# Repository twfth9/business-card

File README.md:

# business-card
Business Card Designs

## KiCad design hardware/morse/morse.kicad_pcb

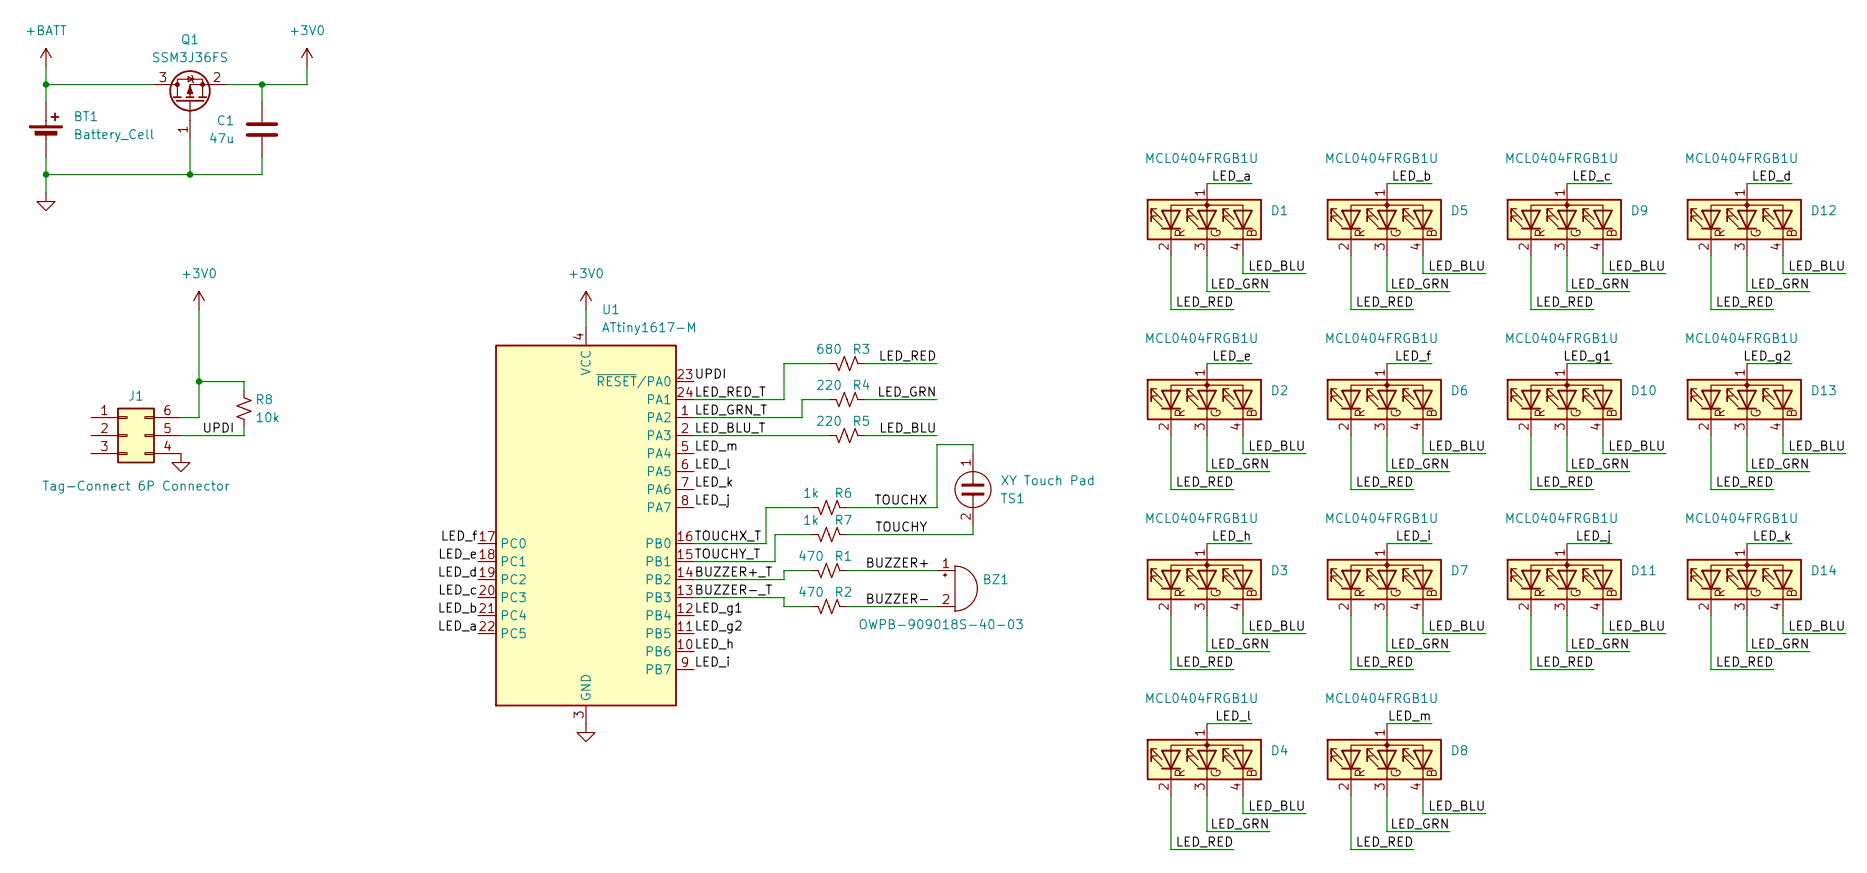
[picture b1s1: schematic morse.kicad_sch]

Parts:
BT1: Battery_Cell; CR2032_Holder
BZ1: OWPB-909018S-40-03; OWPB-909018S_recessed
C1: 47u; C_0805_2012Metric; Partnumber C16780; LCSC C16780
D1, D2, D3, D4, D5, D6, D7, D8, D9, D10, D11, D12, D13, D14: MCL0404FRGB1U; DigiKey 2679-MCL0404FRGB1U-CT-ND
J1: Tag-Connect 6P Connector; TC2030-IDC-NL_6P
Q1: SSM3J36FS; SOT-416; DigiKey SSM3J36FSLFCT-ND
R1, R2: 470; Worthington_R_0402
R3: 680; Worthington_R_0402
R4, R5: 220; Worthington_R_0402
R6, R7: 1k; Worthington_R_0402
R8: 10k
TS1: XY Touch Pad; TouchPad_12mm_XY
U1: ATtiny1617-M; QFN-24-1EP_4x4mm_P0.5mm_EP2.6x2.6mm

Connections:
+3V0: C1.1, J1.6, Q1.2 (S), R8.1, U1.4 (VCC)
+BATT: BT1.1 (+), Q1.3 (D)
/BUZZER+: BZ1.1 (+), R1.2
/BUZZER+_T: R1.1, U1.14 (PB2)
/BUZZER-: BZ1.2 (-), R2.2
/BUZZER-_T: R2.1, U1.13 (PB3)
/LED_BLU: D1.4 (BK), D2.4 (BK), D3.4 (BK), D4.4 (BK), D5.4 (BK), D6.4 (BK), D7.4 (BK), D8.4 (BK), D9.4 (BK), D10.4 (BK), D11.4 (BK), D12.4 (BK), D13.4 (BK), D14.4 (BK), R5.2
/LED_BLU_T: R5.1, U1.2 (PA3)
/LED_GRN: D1.3 (GK), D2.3 (GK), D3.3 (GK), D4.3 (GK), D5.3 (GK), D6.3 (GK), D7.3 (GK), D8.3 (GK), D9.3 (GK), D10.3 (GK), D11.3 (GK), D12.3 (GK), D13.3 (GK), D14.3 (GK), R4.2
/LED_GRN_T: R4.1, U1.1 (PA2)
/LED_RED: D1.2 (RK), D2.2 (RK), D3.2 (RK), D4.2 (RK), D5.2 (RK), D6.2 (RK), D7.2 (RK), D8.2 (RK), D9.2 (RK), D10.2 (RK), D11.2 (RK), D12.2 (RK), D13.2 (RK), D14.2 (RK), R3.2
/LED_RED_T: R3.1, U1.24 (PA1)
/LED_a: D1.1 (A), U1.22 (PC5)
/LED_b: D5.1 (A), U1.21 (PC4)
/LED_c: D9.1 (A), U1.20 (PC3)
/LED_d: D12.1 (A), U1.19 (PC2)
/LED_e: D2.1 (A), U1.18 (PC1)
/LED_f: D6.1 (A), U1.17 (PC0)
/LED_g1: D10.1 (A), U1.12 (PB4)
/LED_g2: D13.1 (A), U1.11 (PB5)
/LED_h: D3.1 (A), U1.10 (PB6)
/LED_i: D7.1 (A), U1.9 (PB7)
/LED_j: D11.1 (A), U1.8 (PA7)
/LED_k: D14.1 (A), U1.7 (PA6)
/LED_l: D4.1 (A), U1.6 (PA5)
/LED_m: D8.1 (A), U1.5 (PA4)
/TOUCHX: R6.2, TS1.1
/TOUCHX_T: R6.1, U1.16 (PB0)
/TOUCHY: R7.2, TS1.2
/TOUCHY_T: R7.1, U1.15 (PB1)
/UPDI: J1.5, R8.2, U1.23 (~RESET/PA0)
GND: BT1.2 (-), C1.2, J1.4, Q1.1 (G), U1.3 (GND), U1.25 (GND)

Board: 2 copper layers, 28 parts (0 on the bottom side), 32 nets, no tracks yet.
